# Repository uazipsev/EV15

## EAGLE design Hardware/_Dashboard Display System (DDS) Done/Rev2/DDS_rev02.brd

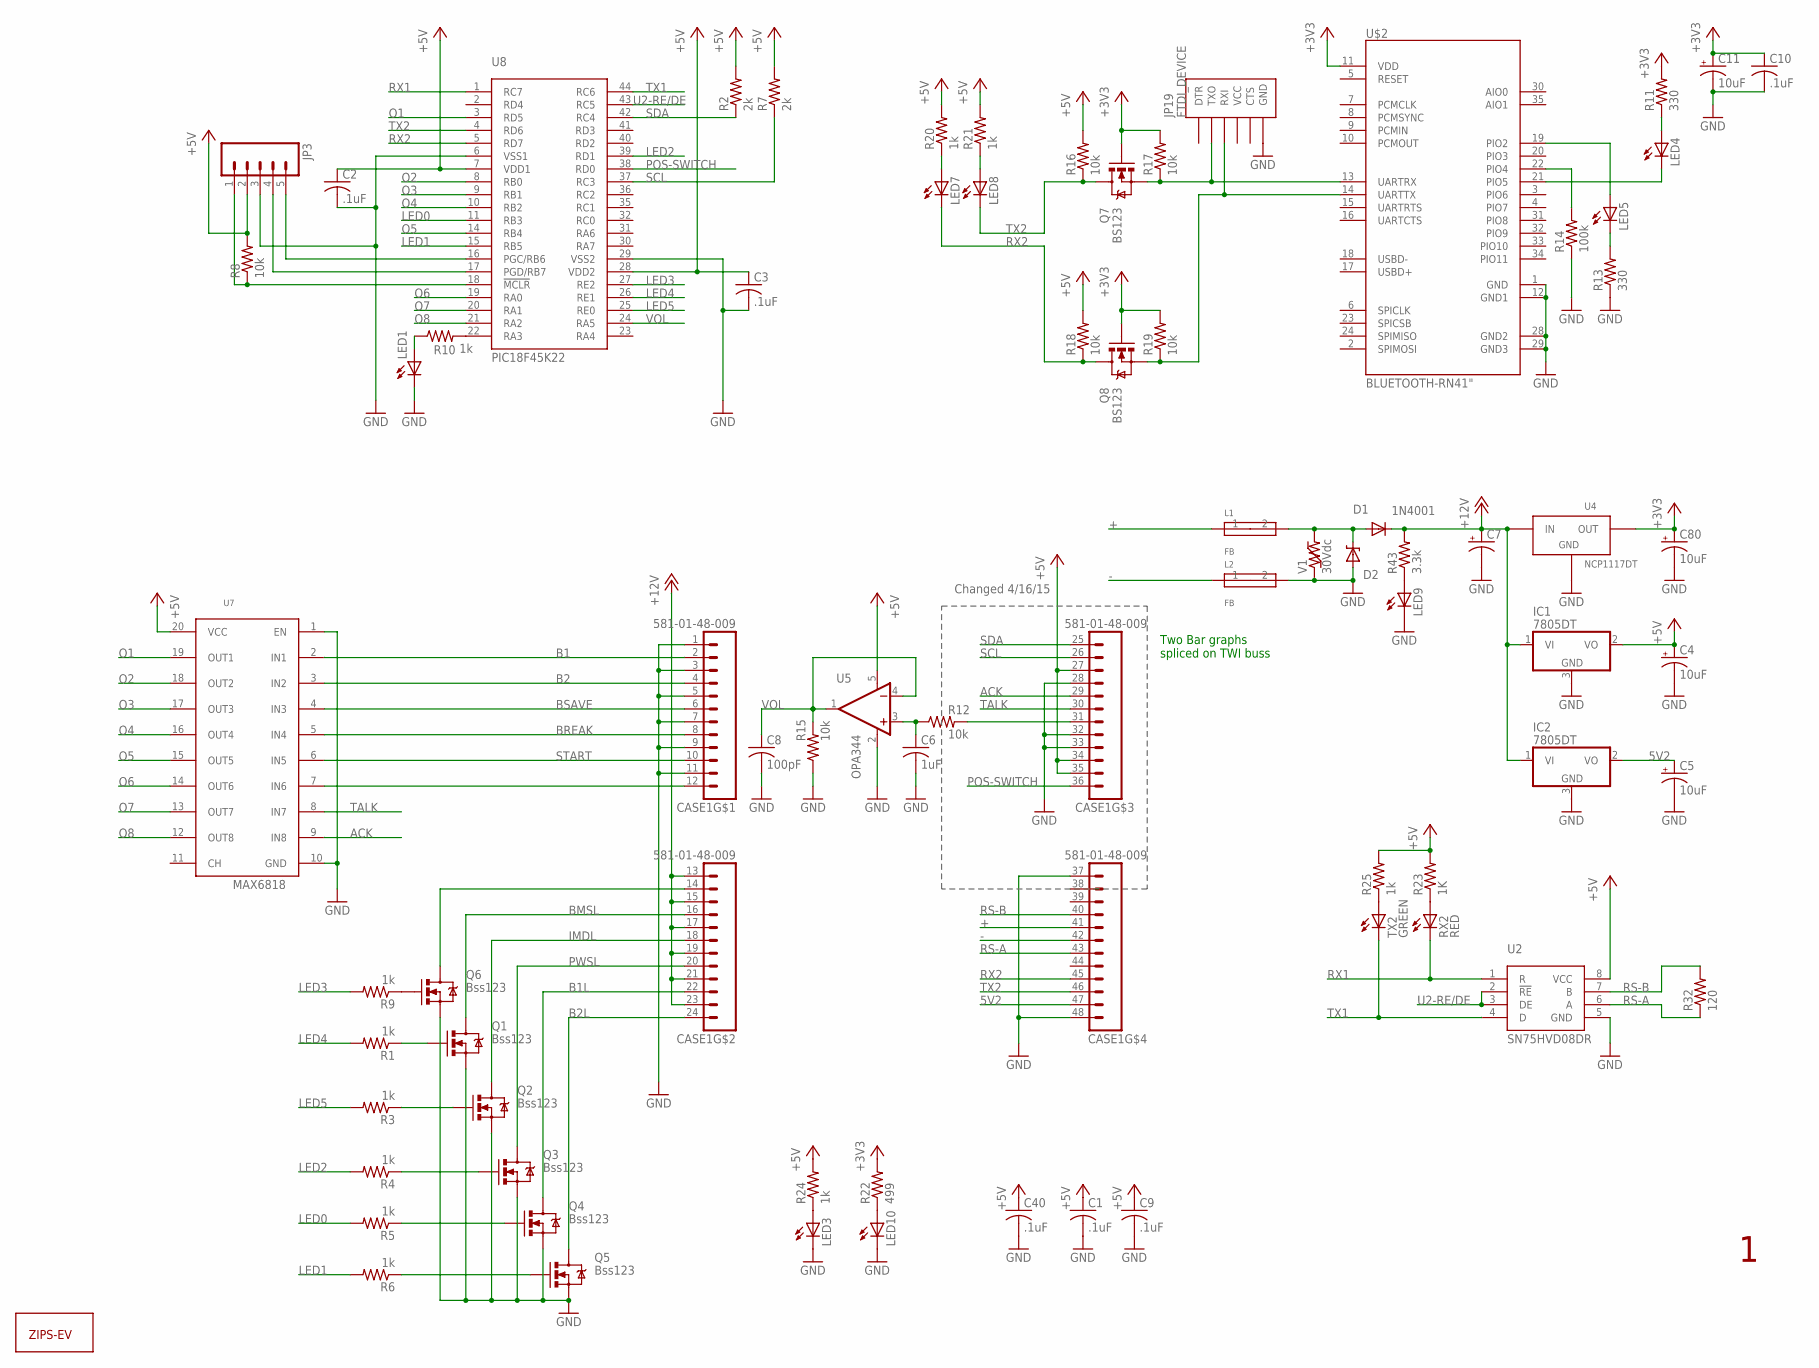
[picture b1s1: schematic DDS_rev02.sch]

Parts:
C1, C2, C3, C9, C10, C40: .1uF; C0805
C4, C5, C11, C80: 10uF; POLC1206
C6: 1uF; C0805
C7: CAP_POL7343; EIA7343
C8: 100pF; C0805
CASE1: 581-01-48-009
D1: 1N4001; SOD123
D2: MM5Z30; SOD-523F
IC1, IC2: 7805DT; TO252
JP3: M05LOCK_LONGPADS; 1X05_LOCK_LONGPADS
JP19: FTDI_DEVICE; FTDI_DEVICE_SIDE
L1, L2: FB; 0603
LED1, LED3, LED4, LED5, LED7, LED8, LED9, LED10: LEDCHIP-LED0805; CHIP-LED0805
Q1, Q2, Q3, Q4, Q5, Q6: Bss123; SOT23
Q7, Q8: BS123; SOT23
R1, R3, R4, R5, R6, R9, R10, R24, R25: 1k; R0805
R2, R7: 2k; R0805
R8, R16, R17, R18, R19: 10k; 0805
R11, R13: 330; 0805
R12, R15: 10k; R0805
R14: 100k; 0805
R20, R21: 1k; 0805
R22: 499; R0805
R23: 1K; R0805
R32: 120; R0805
R43: 3.3k; R0805
RX2: RED; CHIPLED_0805
TX2: GREEN; CHIPLED_0805
U2: SN75HVD08DR; SO-8
U4: NCP1117DT; DPAK
U5: OPA344; SOT23-5
U7: MAX6818; SSOP-20
U8: PIC18F45K22; TQFP-44
U$1: LOGO; L-L
U$2: BLUETOOTH-RN41"; RN41
V1: 30Vdc; 0603

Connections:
5V2: C5.1 (+), CASE1.47 (11), IC2.2 (VO)
+: CASE1.41 (5), L1.1
+3V3: C10.1, C11.1 (+), C80.1 (+), Q7.1 (G), Q8.1 (G), R11.2, R17.2, R19.2, R22.2, U4.2 (OUT), U$2.11 (VDD)
+5V: C1.1, C2.1, C3.1, C4.1 (+), C9.1, C40.1, CASE1.27 (3), CASE1.34 (10), CASE1.35 (11), IC1.2 (VO), JP3.2, R2.2, R7.2, R8.2, R16.2, R18.2, R20.2, R21.2, R23.2, R24.2, R25.2, U2.8 (VCC), U5.5 (V+), U7.20 (VCC), U8.7 (VDD1), U8.28 (VDD2)
+12V: C7.A (+), CASE1.13 (1), CASE1.15 (3), CASE1.17 (5), CASE1.19 (7), CASE1.21 (9), CASE1.23 (11), D1.C, IC1.1 (VI), IC2.1 (VI), R43.2, U4.3 (IN)
-: CASE1.42 (6), L2.1
ACK: CASE1.29 (5), U7.9 (IN8)
B1: CASE1.2, U7.2 (IN1)
B1L: CASE1.22 (10), Q4.3 (D)
B2: CASE1.4, U7.3 (IN2)
B2L: CASE1.24 (12), Q5.3 (D)
BMSL: CASE1.16 (4), Q1.3 (D)
BREAK: CASE1.8, U7.5 (IN4)
BSAVE: CASE1.6, U7.4 (IN3)
GHT: D1.A, D2.C, L1.2, V1.2
GND: C1.2, C2.2, C3.2, C4.2 (-), C5.2 (-), C6.2, C7.C (-), C8.2, C9.2, C10.2, C11.2 (-), C40.2, C80.2 (-), CASE1.1, CASE1.3, CASE1.5, CASE1.7, CASE1.9, CASE1.11, CASE1.28 (4), CASE1.32 (8), CASE1.33 (9), CASE1.37 (1), CASE1.48 (12), D2.A, IC1.3 (GND), IC2.3 (GND), JP3.3, JP19.P$6 (GND), L2.2, LED1.C, LED3.C, LED9.C, LED10.C, Q1.2 (S), Q2.2 (S), Q3.2 (S), Q4.2 (S), Q5.2 (S), Q6.2 (S), R13.1, R14.1, R15.1, U2.5 (GND), U4.1 (GND), U5.2 (V-), U7.1 (EN), U7.10 (GND), U8.6 (VSS1), U8.29 (VSS2), U$2.1 (GND), U$2.12 (GND1), U$2.28 (GND2), U$2.29 (GND3), V1.1
IMDL: CASE1.18 (6), Q2.3 (D)
LED0: R5.2, U8.11 (RB3)
LED1: R6.2, U8.15 (RB5)
LED2: R4.2, U8.39 (RD1)
LED3: R9.2, U8.27 (RE2)
LED4: R1.2, U8.26 (RE1)
LED5: R3.2, U8.25 (RE0)
unnamed: LED1.A, R10.1
unnamed: R10.2, U8.22 (RA3)
unnamed: JP19.P$3 (RXI), Q8.2 (S), R19.1, U$2.14 (UARTTX)
unnamed: CASE1.12, U7.7 (IN6)
unnamed: CASE1.14 (2), Q6.3 (D)
unnamed: LED4.A, R11.1
unnamed: Q6.1 (G), R9.1
unnamed: LED4.C, U$2.21 (PIO5)
unnamed: LED5.A, U$2.19 (PIO2)
unnamed: R14.2, U$2.22 (PIO4)
unnamed: JP19.P$2 (TXO), Q7.2 (S), R17.1, U$2.13 (UARTRX)
unnamed: LED5.C, R13.2
unnamed: LED9.A, R43.1
unnamed: Q1.1 (G), R1.1
unnamed: LED7.A, R20.1
unnamed: LED8.A, R21.1
unnamed: LED10.A, R22.1
unnamed: Q2.1 (G), R3.1
unnamed: Q3.1 (G), R4.1
unnamed: Q4.1 (G), R5.1
unnamed: Q5.1 (G), R6.1
unnamed: CASE1.31 (7), R12.2
unnamed: LED3.A, R24.1
unnamed: C6.1, R12.1, U5.3 (+IN)
unnamed: R25.1, TX2.A
unnamed: R23.1, RX2.A
unnamed: JP3.4, U8.17 (PGD/RB7)
unnamed: JP3.5, U8.16 (PGC/RB6)
unnamed: JP3.1, R8.1, U8.18 (!MCLR)
O1: U7.19 (OUT1), U8.3 (RD5)
O2: U7.18 (OUT2), U8.8 (RB0)
O3: U7.17 (OUT3), U8.9 (RB1)
O4: U7.16 (OUT4), U8.10 (RB2)
O5: U7.15 (OUT5), U8.14 (RB4)
O6: U7.14 (OUT6), U8.19 (RA0)
O7: U7.13 (OUT7), U8.20 (RA1)
O8: U7.12 (OUT8), U8.21 (RA2)
POS-SWITCH: CASE1.36 (12), U8.38 (RD0)
PWSL: CASE1.20 (8), Q3.3 (D)
RS-A: CASE1.43 (7), R32.1, U2.6 (A)
RS-B: CASE1.40 (4), R32.2, U2.7 (B)
RX1: RX2.C, U2.1 (R), U8.1 (RC7)
RX2: CASE1.45 (9), LED7.C, Q8.3 (D), R18.1, U8.5 (RD7)
SCL: CASE1.26 (2), R7.1, U8.37 (RC3)
SDA: CASE1.25 (1), R2.1, U8.42 (RC4)
START: CASE1.10, U7.6 (IN5)
TALK: CASE1.30 (6), U7.8 (IN7)
TX1: TX2.C, U2.4 (D), U8.44 (RC6)
TX2: CASE1.46 (10), LED8.C, Q7.3 (D), R16.1, U8.4 (RD6)
U2-RE/DE: U2.2 (!RE), U2.3 (DE), U8.43 (RC5)
VOL: C8.1, R15.2, U5.1 (OUT), U5.4 (-IN), U8.24 (RA5)

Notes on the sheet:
Changed 4/16/15
Two Bar graphs spliced on TWI buss

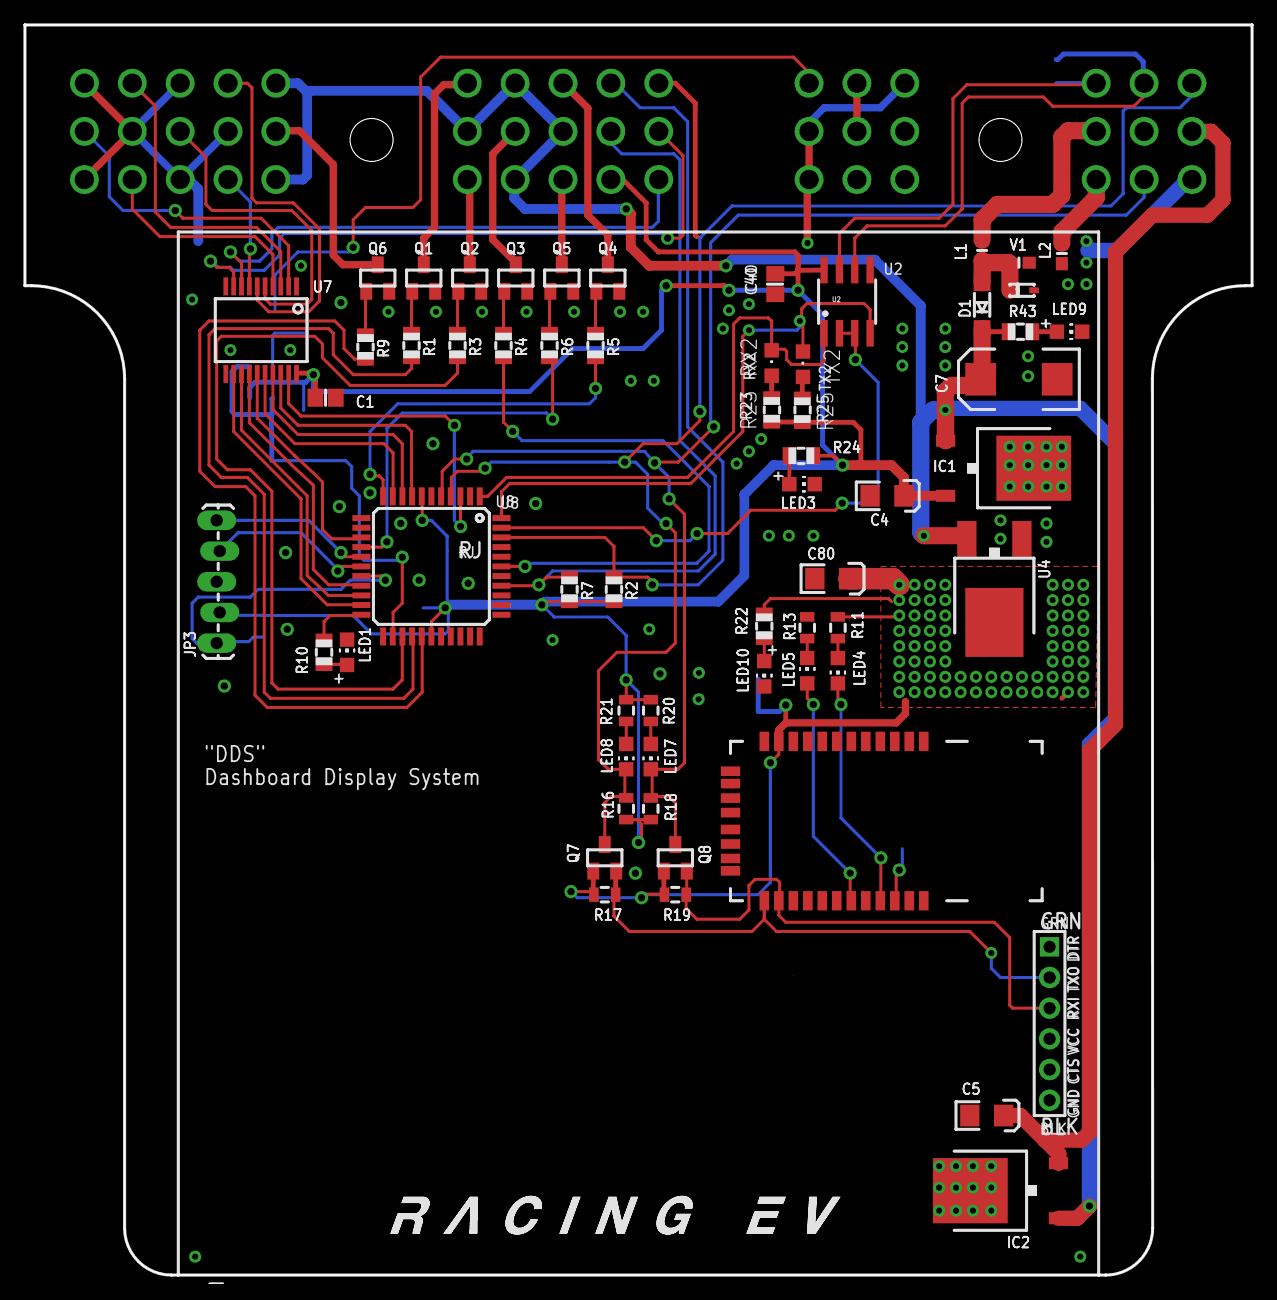
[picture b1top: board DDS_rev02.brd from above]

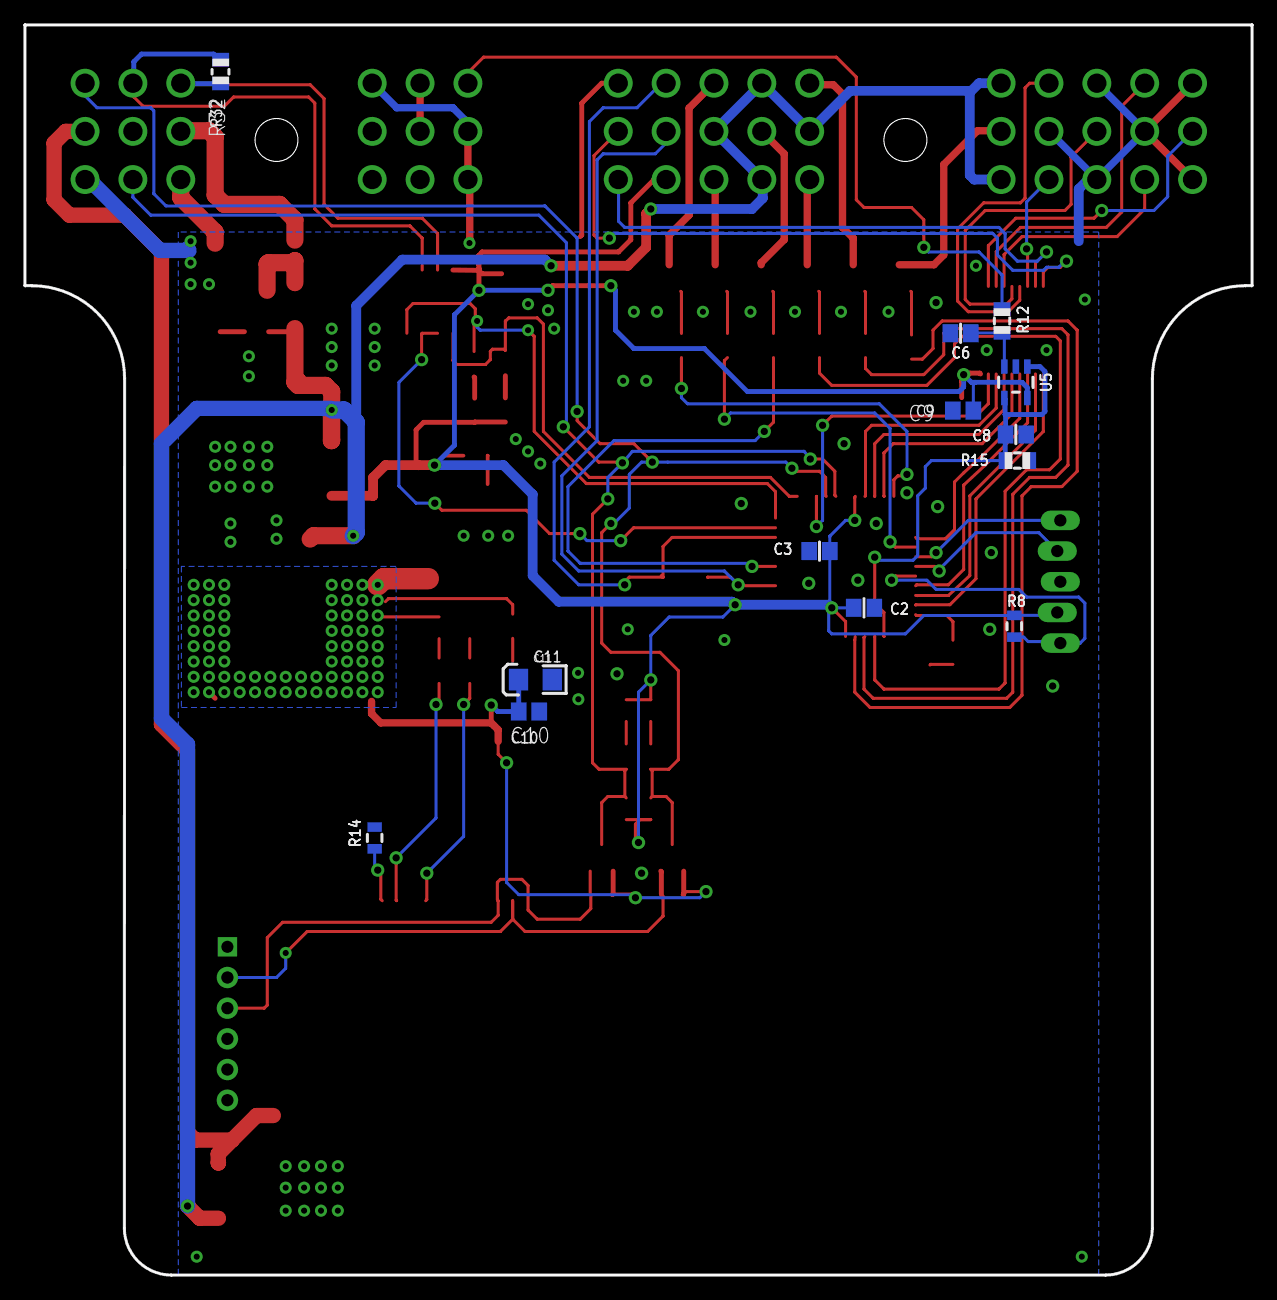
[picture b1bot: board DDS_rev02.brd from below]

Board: 2 copper layers, 101.6 x 103.5 mm, 75 parts (13 on the bottom side), 74 nets.

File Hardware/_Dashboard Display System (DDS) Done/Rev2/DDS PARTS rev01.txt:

Partlist

Exported from DDS_rev01.brd at 1/17/2015 7:30:55 PM

EAGLE Version 6.5.0 Copyright (c) 1988-2013 CadSoft

Assembly variant: 

Part     Value           Package            Library               Position (mil)        Orientation

C1       .1uF            C0805              adafruit              (480 2860)            R0
C2       .1uF            C0805              adafruit              (765 2175)            MR0
C3       .1uF            C0805              adafruit              (910 2360)            MR180
C4       10uF            POLC1206           RJ's_parts            (2310 2540)           R180
C5       10uF            POLC1206           RJ's_parts            (2635 520)            R180
C6       1uF             C0805              adafruit              (450 3070)            MR180
C7                       EIA7343            SparkFun-Capacitors   (2740 2920)           R180
C8       100pF           C0805              adafruit              (270 2740)            MR0
C9       .1uF            C0805              adafruit              (442 2818)            MR180
C10      .1uF            C0805              adafruit              (1857 1837)           MR0
C11      10uF            POLC1206           RJ's_parts            (1836 1941)           MR0
C40      .1uF            C0805              adafruit              (1946 3230.5)         R270
C80      10uF            POLC1206           RJ's_parts            (2130 2270)           R180
CASE1    581-01-48-009   581-01-48-009      FSAE Eletric          (1500 3700)           R0
D1       1N4001          SOD123             diode                 (2620 3160)           R90
D2       MM5Z30          SOD-523F           EmEndev               (2750 3210)           R180
IC1      7805DT          TO252              adafruit              (2690 2630)           R270
IC2      7805DT          TO252              adafruit              (2680 275)            R90
JP3                      1X05_LOCK_LONGPADS SparkFun-Connectors   (125 2060)            R90
JP19     FTDI_DEVICE     FTDI_DEVICE_SIDE   SparkFun-Connectors   (2840 820)            R270
L1       FB              0603               EmEndev               (2620 3340)           R270
L2       FB              0603               EmEndev               (2880 3330)           R270
LED1                     CHIP-LED0805       adafruit              (550 2030)            R0
LED3                     CHIP-LED0805       adafruit              (2033 2578)           R270
LED4                     CHIP-LED0805       led                   (2150 1970)           R180
LED5                     CHIP-LED0805       led                   (2050 1970)           R0
LED7                     CHIP-LED0805       led                   (1540 1690)           R180
LED8                     CHIP-LED0805       led                   (1460 1690)           R180
LED9                     CHIP-LED0805       adafruit              (2905 3075)           R270
LED10                    CHIP-LED0805       adafruit              (1910 1960)           R180
Q1       Bss123          SOT23              SparkFun-DiscreteSemi (800 3250)            R0
Q2       Bss123          SOT23              SparkFun-DiscreteSemi (950 3250)            R0
Q3       Bss123          SOT23              SparkFun-DiscreteSemi (1100 3250)           R0
Q4       Bss123          SOT23              SparkFun-DiscreteSemi (1400 3250)           R0
Q5       Bss123          SOT23              SparkFun-DiscreteSemi (1250 3250)           R0
Q6       Bss123          SOT23              SparkFun-DiscreteSemi (650 3250)            R0
Q7       BS123           SOT23              SparkFun-DiscreteSemi (1390 1360)           R0
Q8       BS123           SOT23              SparkFun-DiscreteSemi (1620 1360)           R0
R1       1k              R0805              adafruit              (760 3030)            R270
R2       2k              R0805              adafruit              (1420 2235)           R270
R3       1k              R0805              adafruit              (910 3030)            R270
R4       1k              R0805              adafruit              (1060 3030)           R270
R5       1k              R0805              adafruit              (1360 3030)           R270
R6       1k              R0805              adafruit              (1210 3030)           R270
R7       2k              R0805              adafruit              (1275 2235)           R270
R8       10k             0805               SparkFun-Passives     (275 2115)            MR90
R9       1k              R0805              adafruit              (610 3025)            R270
R10      1k              R0805              adafruit              (475 2030)            R90
R11      330             0805               SparkFun-Passives     (2150 2110)           R90
R12      10k             R0805              adafruit              (315 3110)            MR90
R13      330             0805               SparkFun-Passives     (2050 2110)           R270
R14      100k            0805               SparkFun-Passives     (2360 1425)           MR270
R15      10k             R0805              adafruit              (265 2655)            MR180
R16      10k             0805               SparkFun-Passives     (1460 1520)           R270
R17      10k             0805               SparkFun-Passives     (1390 1240)           R180
R18      10k             0805               SparkFun-Passives     (1540 1520)           R270
R19      10k             0805               SparkFun-Passives     (1620 1240)           R180
R20      1k              0805               SparkFun-Passives     (1540 1840)           R90
R21      1k              0805               SparkFun-Passives     (1460 1840)           R90
R22      499             R0805              adafruit              (1910 2115)           R90
R23      1K              R0805              adafruit              (1934 2820)           R270
R24      1k              R0805              adafruit              (2031 2671)           R0
R25      1k              R0805              adafruit              (2034 2819)           R270
R32      120             R0805              adafruit              (2482 3813)           MR270
R43      3.3k            R0805              adafruit              (2745 3075)           R180
RX2      RED             CHIPLED_0805       adafruit              (1934 2973)           R0
TX2      GREEN           CHIPLED_0805       adafruit              (2036 2969)           R0
U$2      BLUETOOTH-RN41" RN41               SparkFun-RF           (2170 1480)           R180
U2       SN75HVD08DR     SO-8               FSAE Eletric          (2180 3173)           R0
U4       NCP1117DT       DPAK               FSAE Eletric          (2660 2240)           R180
U5       OPA344          SOT23-5            SparkFun-AnalogIC     (270 2910)            MR180
U7       MAX6818         SSOP-20            NASA_LIB              (270 3080)            R180
U8       PIC18F45K22     TQFP-44            FSAE Eletric          (825 2310)            R270
V1       30Vdc           0603               EmEndev               (2740 3300)           R180

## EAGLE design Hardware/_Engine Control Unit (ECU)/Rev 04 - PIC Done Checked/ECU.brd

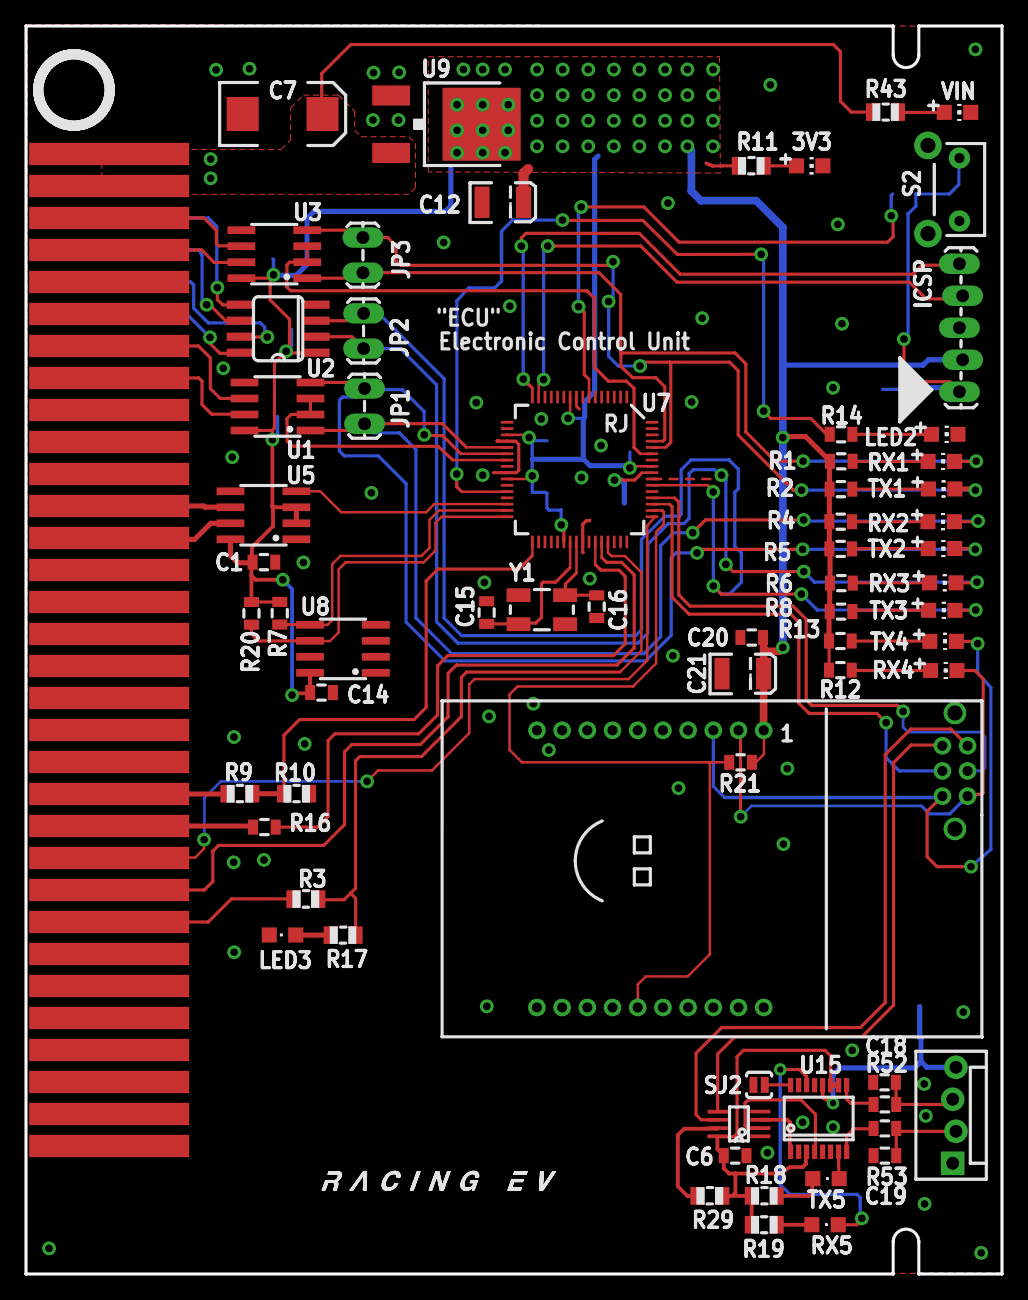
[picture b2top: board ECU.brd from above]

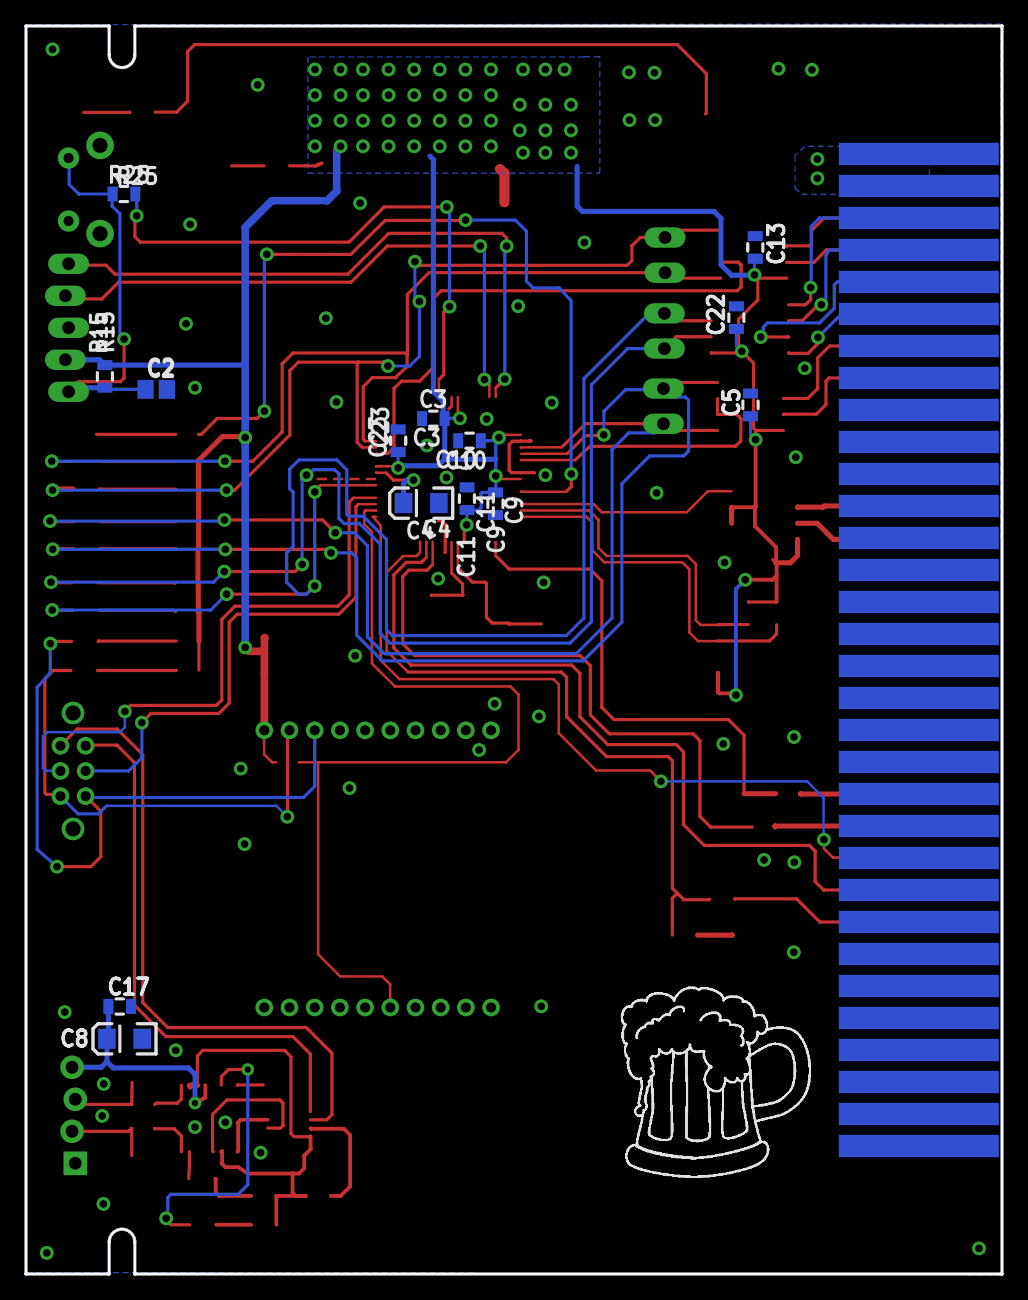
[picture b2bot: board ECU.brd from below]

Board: 2 copper layers, 77.5 x 99.1 mm, 86 parts (16 on the bottom side), 73 nets.

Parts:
3V3: CHIP-LED0805
C1, C3, C5, C9, C10, C11, C13, C14, C20, C22, C23: 0.1uF; 0805
C2: 10n; C0805
C4: 10uF; EIA3216
C6, C17: 0.1uf; 0805
C7: 10uF; EIA7343
C8: 4.7uF; EIA3216
C12, C21: 10uf; EIA3528
C15, C16: 12pF; 0805
C18, C19: 47pf; 0805
CARD1: CARD; CARD-64
ICSP: ICSP; 1X05_LOCK_LONGPADS
JP1, JP2, JP3: M02LOCK_LONGPADS; 1X02_LOCK_LONGPADS
JP13: MOLEX-1X4_LOCK
LED2: CHIP-LED0805
LED3: Green; CHIPLED_0805
R1, R2, R4, R5, R6, R8, R12, R13, R16, R21: 1k; 0805
R3: 0; R0805
R7, R20: 2k; 0805
R9: 30k; R0805
R10: 10k; R0805
R11: 499; R0805
R14, R25: 499; 0805
R15: 10k; 0805
R17, R19, R43: 1k; R0805
R18, R29: 1K; R0805
R52, R53: 27; 0805
RX1, RX2, RX3, RX4: CHIP-LED0805
RX5: CHIPLED_0805
S1: EG2211
S2: ts; TACTILE-PTH-SIDEEZ
SJ2: PAD-JUMPER-2-NO_YES_SILK
TX1, TX2, TX3, TX4: CHIP-LED0805
TX5: CHIPLED_0805
U1, U3, U5: SN75HVD08DR; SO-8
U2: ISL83077; SO08
U4: SN74LVC2G241DCTR; VFSOP-8
U6: RM024; RM024-TH
U7: DSPIC33EP256GM306; TQFP-64
U8: CAT24M01WI-GT3; SO08
U9: NCP1117DT33T5G; V-REG_DPACK
U15: FT230X; SSOP-16
U$1: INDPK1; PICKIT-PIN-1
U$2: LOGOM; L-M
U$3: BEERM; B-M
VIN: CHIP-LED0805
Y1: 12Mhz; CRYSTAL-SMD-5X3

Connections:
3V: C6.1, R18.2, R19.2, R29.2, U4.8, U15.3, U15.10, U15.11
+3V3: C1.1, C3.1, C5.1, C9.1, C10.1, C11.2, C12.A, C13.1, C14.1, C20.1, C21.A, C22.1, C23.1, ICSP.2, R1.1, R2.1, R4.1, R5.1, R6.1, R7.2, R8.1, R11.2, R12.1, R13.1, R15.2, R20.2, R21.1, U1.8, U2.1, U3.8, U5.2, U5.3, U5.8, U6.1, U7.10, U7.19, U7.26, U7.38, U7.57, U8.8, U9.4
+9V: C7.A, CARD1.1, CARD1.2, CARD1.33, CARD1.34, R43.2, U9.3
BRAKELIGHT: CARD1.24, U7.44
ECU-SS-IN: CARD1.21, R9.2
GND: 3V3.C, C1.2, C2.2, C3.2, C4.C, C5.2, C6.2, C7.C, C8.C, C9.2, C10.2, C11.1, C12.C, C13.2, C14.2, C15.2, C16.2, C17.2, C18.2, C19.2, C20.2, C21.C, C22.2, C23.2, CARD1.31, CARD1.32, CARD1.63, CARD1.64, ICSP.3, JP13.1, LED2.C, LED3.C, R10.1, S2.1, SJ2.1, U1.5, U2.4, U3.5, U4.1, U4.4, U5.1, U5.5, U6.10, U7.9, U7.20, U7.25, U7.41, U8.1, U8.2, U8.3, U8.4, U8.7, U9.1, U15.5, U15.13, VIN.C
HORN: CARD1.22, R16.1
HORNEN: CARD1.23, U7.49
INRG: R21.2, U6.15, U7.50
LED-A: CARD1.12, U5.6
LED-B: CARD1.13, U5.7
LED-DATA: U5.4, U7.30
unnamed: R14.2, U7.28
unnamed: 3V3.A, R11.1
unnamed: R18.1, TX5.A
unnamed: R4.2, RX2.A
unnamed: R5.2, TX2.A
unnamed: R1.2, RX1.A
unnamed: R2.2, TX1.A
unnamed: R6.2, RX3.A
unnamed: R8.2, TX3.A
unnamed: R12.2, RX4.A
unnamed: R13.2, TX4.A
unnamed: C16.1, U7.40, Y1.3
unnamed: C15.1, U7.39, Y1.1
unnamed: LED2.A, R14.1
unnamed: R7.1, U7.31, U8.5
unnamed: R19.1, RX5.A
unnamed: TX5.C, U15.7
unnamed: RX5.C, U15.14
unnamed: U4.2, U15.4
unnamed: U4.3, U15.1
unnamed: R52.2, U15.9
unnamed: R20.1, U7.32, U8.6
unnamed: R43.1, VIN.A
unnamed: LED3.A, R17.1
unnamed: R53.2, U15.8
unnamed: C18.1, JP13.3, R52.1
unnamed: C19.1, JP13.2, R53.1
unnamed: SJ2.2, U15.16
unnamed: R29.1, U4.7
unnamed: C8.A, C17.1, JP13.4, U15.12
unnamed: C2.1, ICSP.1, R15.1, R25.1, S2.2
unnamed: R25.2, U7.7
unnamed: C4.A, U7.56
unnamed: ICSP.4, U7.15
unnamed: ICSP.5, U7.16
RS485-1-A: CARD1.3, U3.6
RS485-1-B: CARD1.4, U3.7
RS485-2-A: CARD1.7, U1.6
RS485-2-B: CARD1.8, U1.7
RS-TM-A: CARD1.38, U2.8
RS-TM-B: CARD1.37, U2.7
RS-TM-Y: CARD1.35, U2.5
RS-TM-Z: CARD1.36, U2.6
RTD-HORN: R16.2, U7.43
RX: S1.P1, U7.52
RXD0: JP3.2, RX1.C, U3.1, U7.61
RXD1: JP1.2, RX2.C, U1.1, U7.21
RXD2: JP2.2, RX3.C, U2.2, U7.55
RXD3: S1.P1-TA, U4.6
RXD4: RX4.C, S1.P1-TB, U6.2
SS: R3.2, R17.2, U7.45
SS-D: R9.1, R10.2, U7.33
SS-ECU-RELAY: CARD1.25, R3.1
TX: S1.P2, U7.51
TXD0: JP3.1, TX1.C, U3.4, U7.60
TXD1: JP1.1, TX2.C, U1.4, U7.22
TXD2: JP2.1, TX3.C, U2.3, U7.54
TXD3: S1.P2-TA, U4.5
TXD4: S1.P2-TB, TX4.C, U6.3
U1-EN: U1.2, U1.3, U7.23
U3-EN: U3.2, U3.3, U7.59

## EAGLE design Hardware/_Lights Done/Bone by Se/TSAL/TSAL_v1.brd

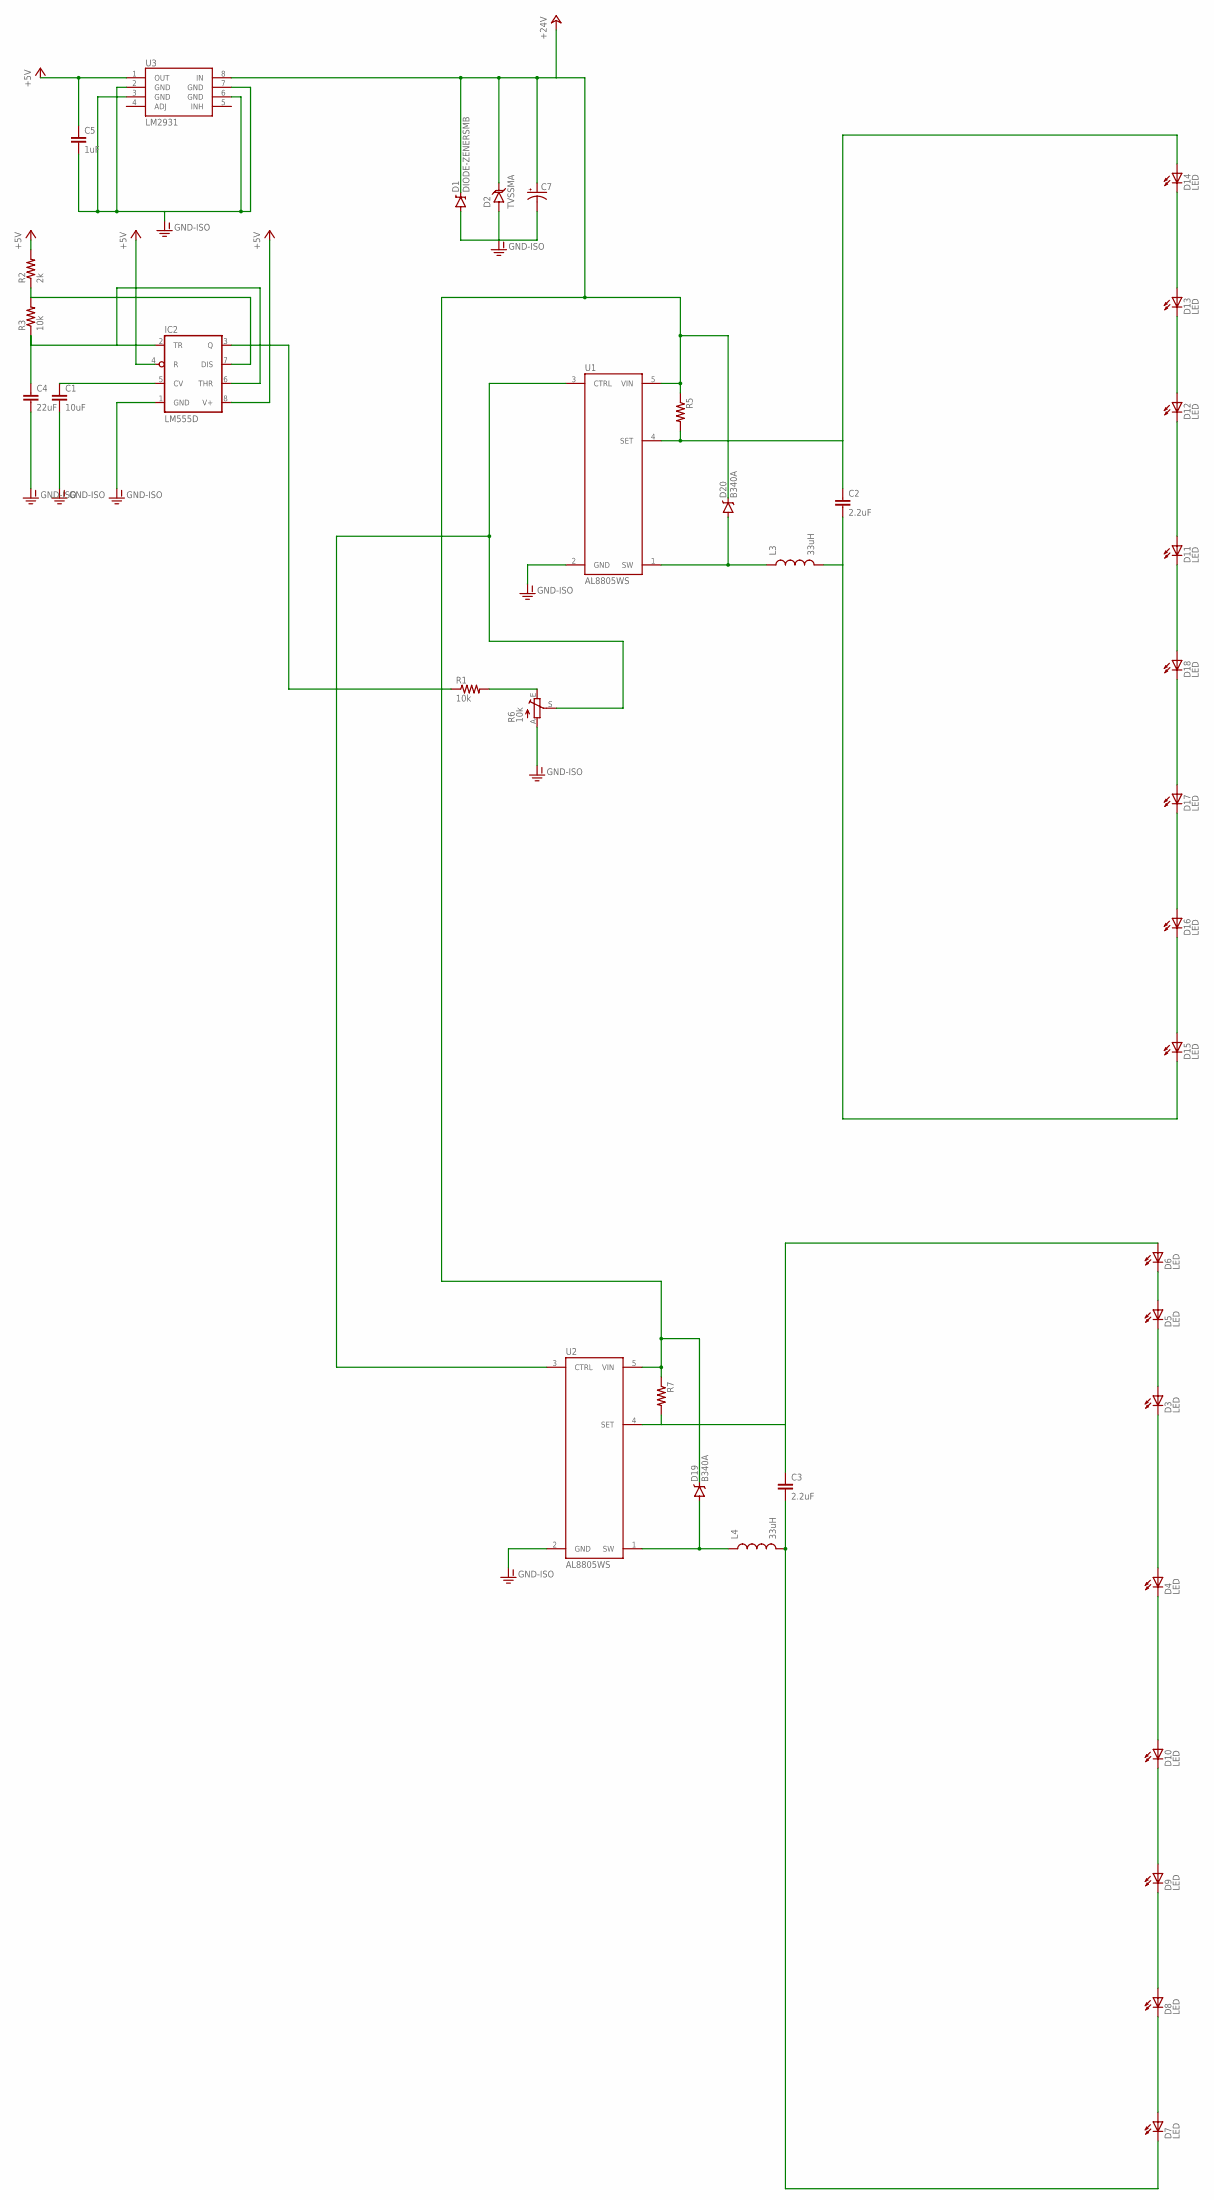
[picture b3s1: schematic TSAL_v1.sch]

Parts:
C1: 10uF; 0805
C2, C3: 2.2uF; 0805
C4: 22uF; 0805
C5: 1uF; 0805
C7: CAP_POL6032; EIA6032
D1: DIODE-ZENERSMB; SMB-DIODE
D2: TVSSMA; SMA-DIODE
D3, D4, D5, D6, D7, D8, D9, D10, D11, D12, D13, D14, D15, D16, D17, D18: LED; LED-SM
D19, D20: B340A; SMA-DIODE
IC2: LM555D; SO08
L3, L4: 33uH; SRN6045
R1, R3: 10k; 0805
R2: 2k; 0805
R5, R7: RESISTOR0805-RES; 0805
R6: 10k; B25P
U1, U2: AL8805WS; SOT23-5
U3: LM2931; SO08

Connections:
+5V: C5.1, IC2.4 (R), IC2.8 (V+), R2.2, U3.1 (OUT)
+24V: C7.P$1 (+), D1.C, D2.C, D19.C, D20.C, R5.1, R7.1, U1.5 (VIN), U2.5 (VIN), U3.8 (IN)
GND-ISO: C1.2, C4.2, C5.2, C7.P$2 (-), D1.A, D2.A, IC2.1 (GND), R6.A, U1.2 (GND), U2.2 (GND), U3.2 (GND), U3.3 (GND), U3.6 (GND), U3.7 (GND)
unnamed: C3.1, D6.A, R7.2, U2.4 (SET)
unnamed: R6.S, U1.3 (CTRL), U2.3 (CTRL)
unnamed: D3.C, D4.A
unnamed: C1.1, IC2.5 (CV)
unnamed: IC2.7 (DIS), R2.1, R3.2
unnamed: IC2.3 (Q), R1.1
unnamed: D19.A, L4.1, U2.1 (SW)
unnamed: C2.1, D14.A, R5.2, U1.4 (SET)
unnamed: D13.A, D14.C
unnamed: C4.1, IC2.2 (TR), IC2.6 (THR), R3.1
unnamed: D3.A, D5.C
unnamed: D12.A, D13.C
unnamed: D11.A, D12.C
unnamed: C3.2, D7.C, L4.2
unnamed: D11.C, D18.A
unnamed: D17.A, D18.C
unnamed: D5.A, D6.C
unnamed: D7.A, D8.C
unnamed: C2.2, D15.C, L3.2
unnamed: D8.A, D9.C
unnamed: D4.C, D10.A
unnamed: D9.A, D10.C
unnamed: D16.A, D17.C
unnamed: D15.A, D16.C
unnamed: D20.A, L3.1, U1.1 (SW)
unnamed: R1.2, R6.E

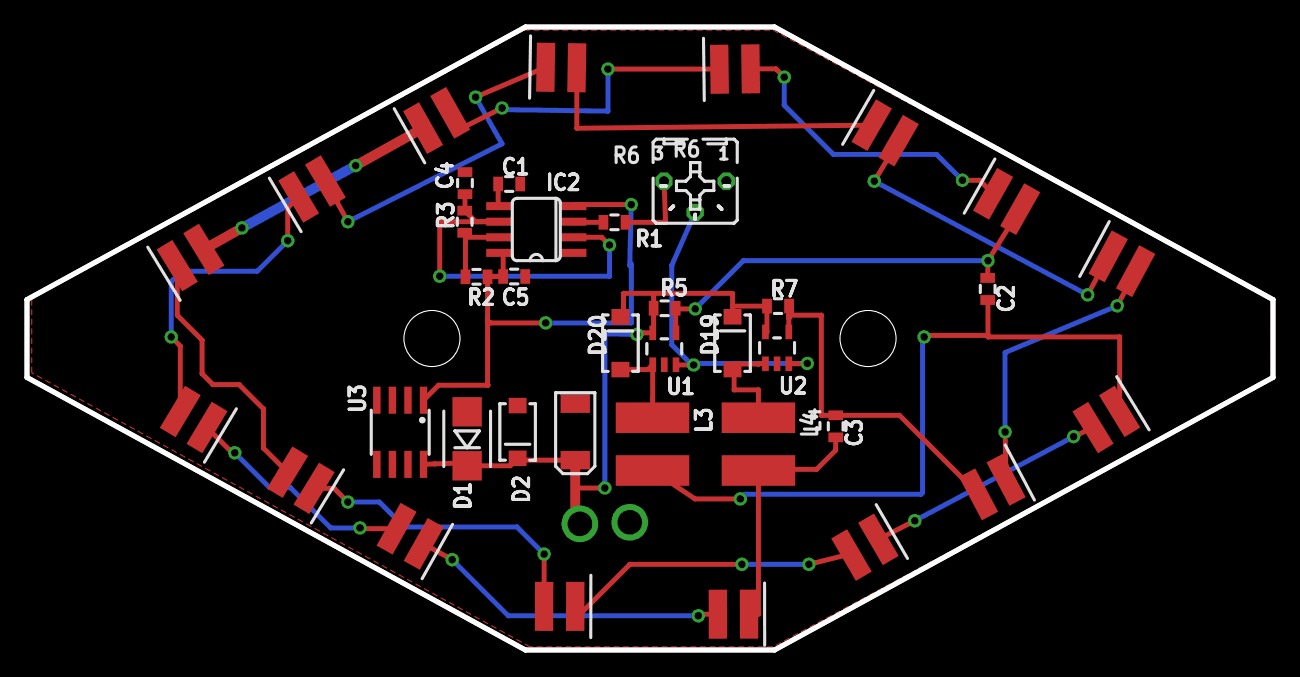
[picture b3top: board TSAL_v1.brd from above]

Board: 2 copper layers, 101.6 x 50.8 mm, 38 parts (0 on the bottom side), 29 nets.

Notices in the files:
parts and their libraries:
SparkFun-DiscreteSemi: Licensing: CC v3.0 Share-Alike You are welcome to use this library for commercial purposes.
SparkFun-RF: Licensing: Creative Commons ShareAlike 4.0 International - https://creativecommons.org/licenses/by-sa/4.0
